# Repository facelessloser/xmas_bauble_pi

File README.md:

# xmas_bauble_pi
xmas_bauble_pi

Blog post - https://facelesstech.wordpress.com/2018/12/02/xmas-bauble-pi/
Youtube - https://www.youtube.com/watch?v=6JN_Shpx8XM

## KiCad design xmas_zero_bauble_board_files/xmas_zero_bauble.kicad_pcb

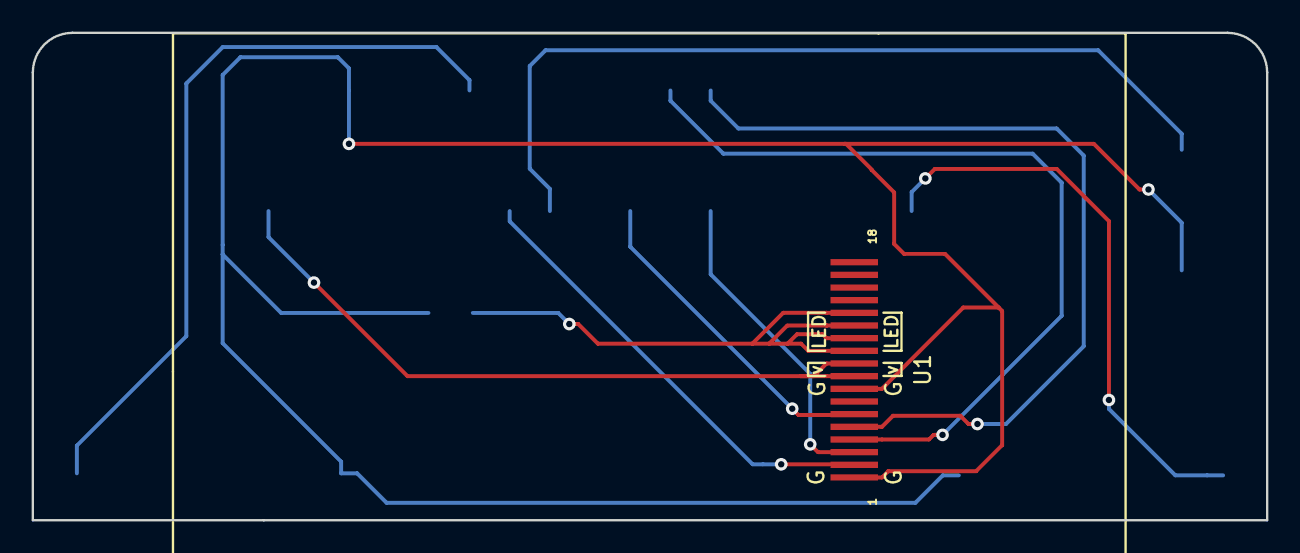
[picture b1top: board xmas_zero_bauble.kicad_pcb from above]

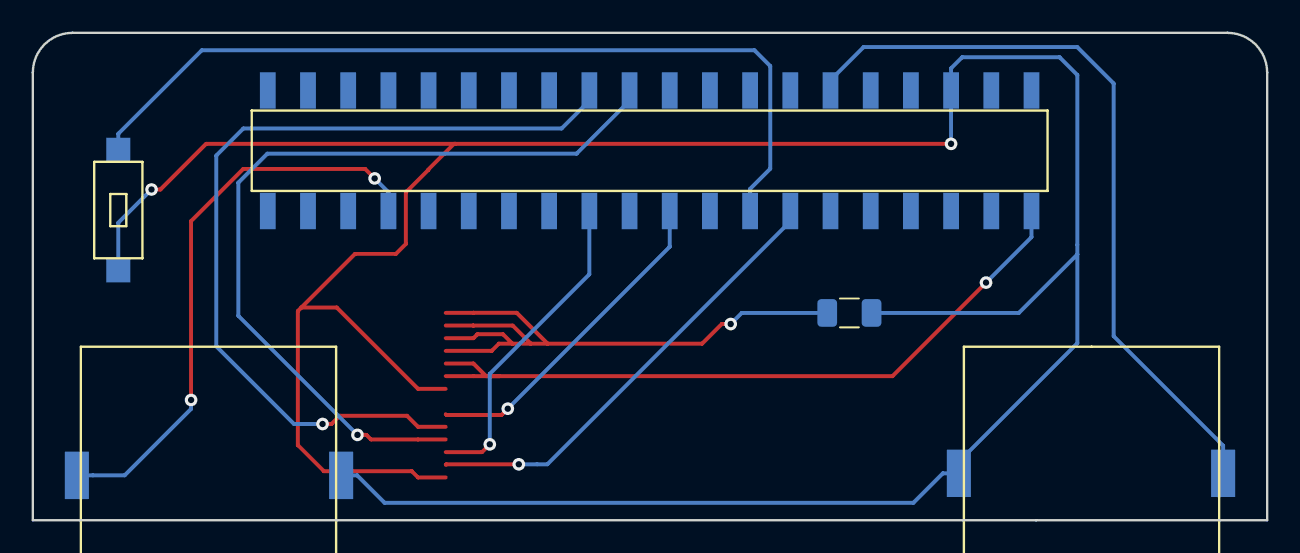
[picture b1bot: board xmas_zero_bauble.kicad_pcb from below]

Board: 2 copper layers, 78.0 x 30.8 mm, 6 parts (5 on the bottom side), 11 nets.

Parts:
J1: Raspberry_Pi_2_3; raspberry_pi_gpio_smd_custom
LS1, LS2: Speaker; piezo_smd
R1: R; R_1206_3216Metric
SW1: SW_Push; SMD_2pin_button_custom
U1: 2.4_screen_ribbon; 2.4_screen_ribbon_breakout

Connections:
unnamed: J1.1, U1.9, U1.10
unnamed: J1.6, LS1.2, LS2.2, R1.2, SW1.1, U1.1, U1.8
unnamed: J1.12, LS2.1
unnamed: J1.13, U1.2
unnamed: J1.15, SW1.2
unnamed: J1.19, U1.6
unnamed: J1.22, U1.4
unnamed: J1.23, U1.3
unnamed: J1.24, U1.5
unnamed: J1.33, LS1.1
unnamed: R1.1, U1.11, U1.12, U1.13, U1.14

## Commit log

2018-12-01 auto play video script
2018-12-02 board files
2018-12-02 added links
2019-12-11 design and sti files
